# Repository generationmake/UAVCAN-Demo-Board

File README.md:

# UAVCAN-Demo-Board
Board for Arduino Nano 33 IoT and with MCP2515 to demonstrate the functions of UAVCAN

## PCB

### Top

### Bottom

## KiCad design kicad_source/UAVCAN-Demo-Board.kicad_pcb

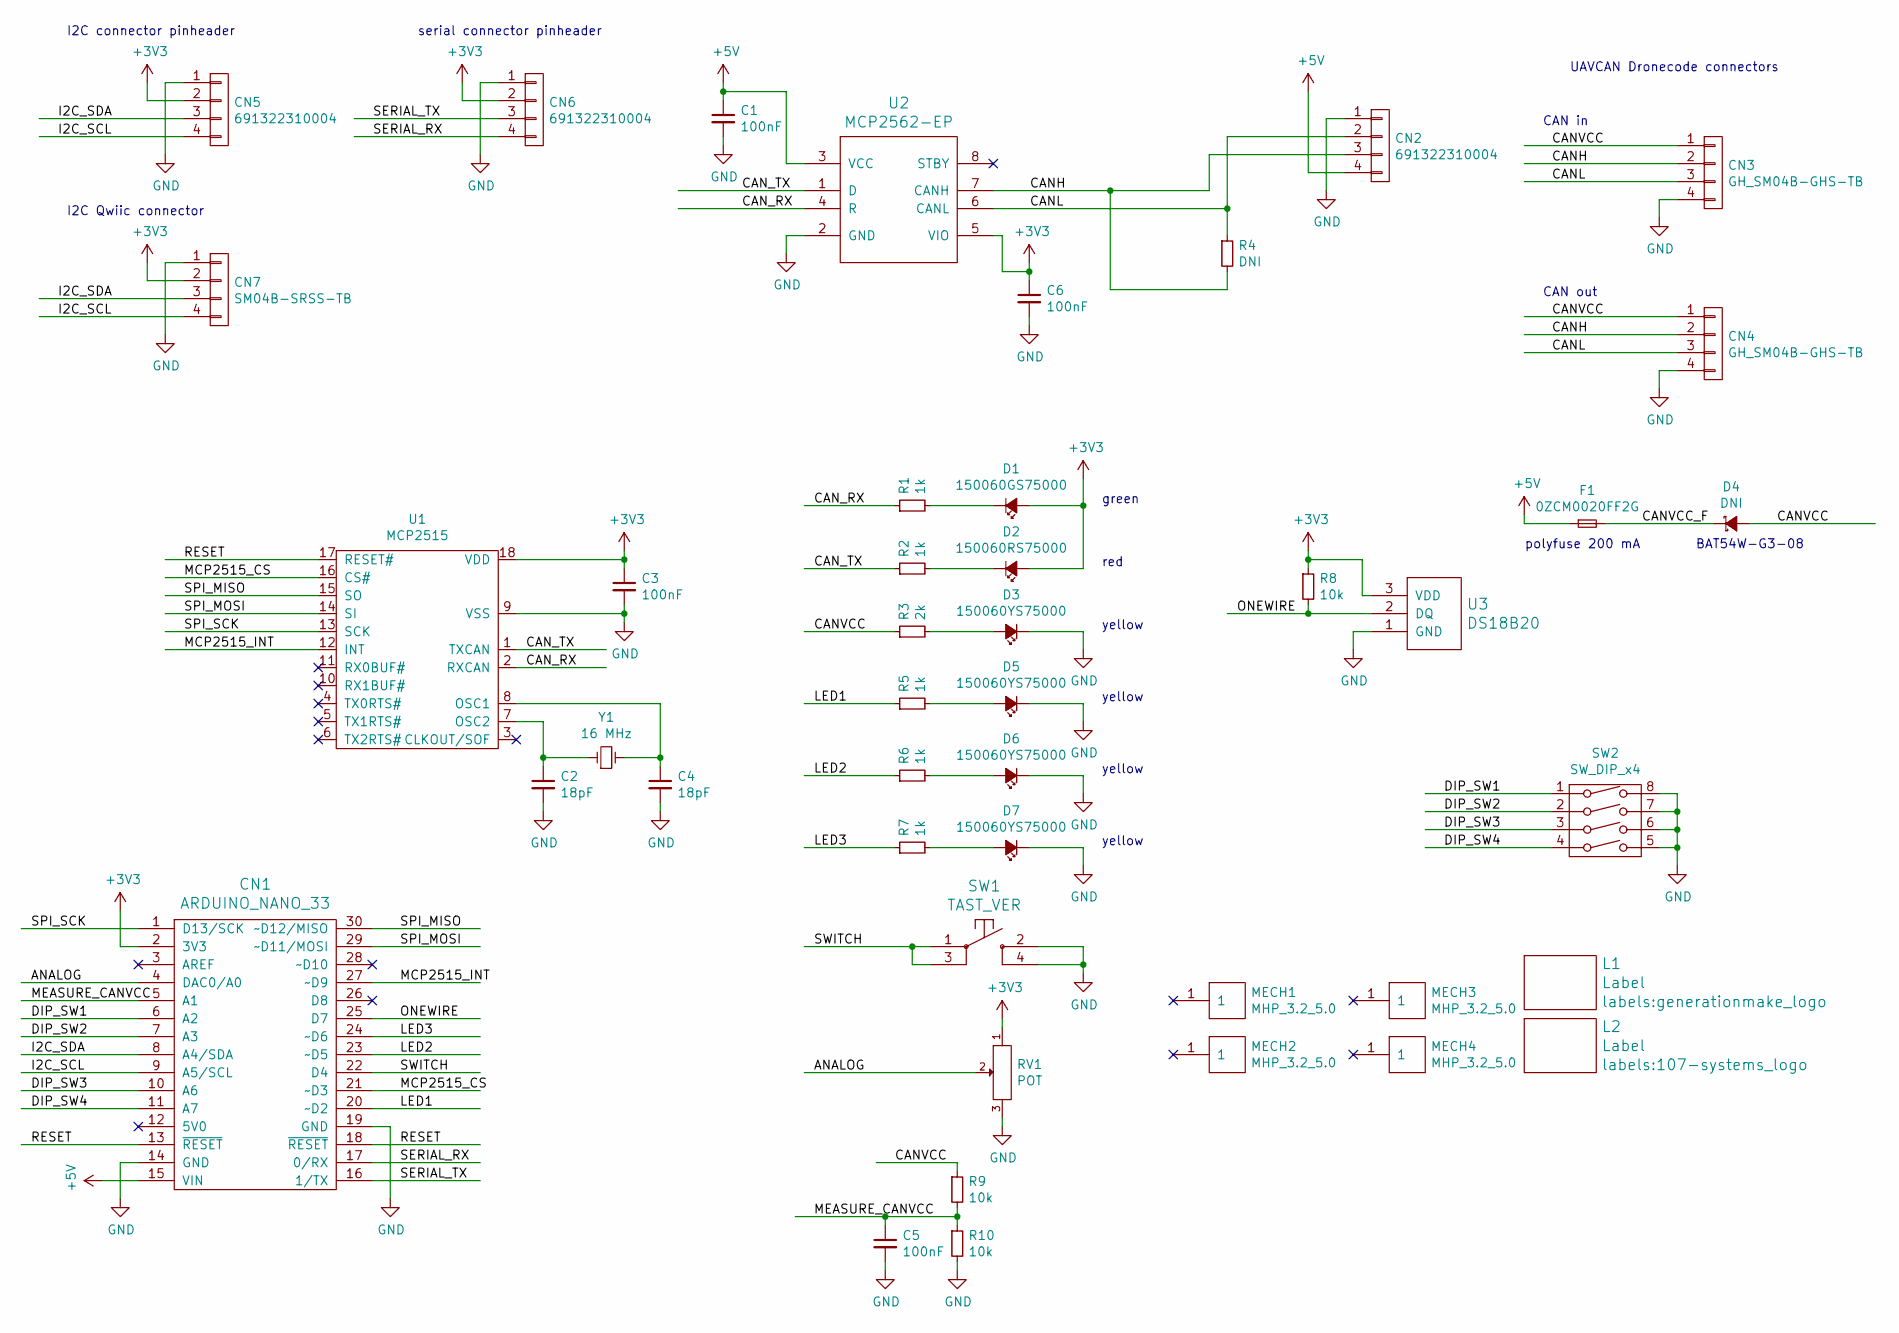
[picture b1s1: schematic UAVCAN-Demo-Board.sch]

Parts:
C1, C3, C5, C6: 100nF; C_Disc_D3.8mm_W2.6mm_P2.50mm
C2, C4: 18pF; C_Disc_D3.8mm_W2.6mm_P2.50mm
CN1: ARDUINO_NANO_33
CN2: 691322310004; WR-TBL_691322310004
CN3, CN4: GH_SM04B-GHS-TB; JST_GH_SM04B-GHS-TB_1x04-1MP_P1.25mm_Horizontal
CN5, CN6: 691322310004; Pin_Header_Straight_1x04
CN7: SM04B-SRSS-TB; JST_SH_SM04B-SRSS-TB_1x04-1MP_P1.00mm_Horizontal
D1: 150060GS75000; LED-5MM
D2: 150060RS75000; LED-5MM
D3, D5, D6, D7: 150060YS75000; LED-5MM
D4: DNI; D_DO-41_SOD81_P7.62mm_Horizontal
F1: 0ZCM0020FF2G; R_Axial_DIN0207_L6.3mm_D2.5mm_P5.08mm_Vertical
L1: Label; generationmake_logo
L2: Label; 107-systems_logo
MECH1, MECH2, MECH3, MECH4: MHP_3.2_5.0
R1, R2, R5, R6, R7: 1k; R_Axial_DIN0207_L6.3mm_D2.5mm_P7.62mm_Horizontal
R3: 2k; R_Axial_DIN0207_L6.3mm_D2.5mm_P7.62mm_Horizontal
R4: DNI; R_Axial_DIN0207_L6.3mm_D2.5mm_P7.62mm_Horizontal
R8, R9, R10: 10k; R_Axial_DIN0207_L6.3mm_D2.5mm_P7.62mm_Horizontal
RV1: POT; Potentiometer_Piher_PT-10-V10_Vertical
SW1: TAST_VER; PCB_PUSH
SW2: SW_DIP_x4; dip_4-300
U1: MCP2515; DIP-18_W7.62mm
U2: MCP2562-EP; DIP-8_W7.62mm
U3: DS18B20; TO-92
Y1: 16 MHz; Crystal_HC49-U_Vertical

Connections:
+3V3: C3.1, C6.1, CN1.2 (3V3), CN5.2, CN6.2, CN7.2, D1.2 (A), D2.2 (A), R8.1, RV1.1, U1.18 (VDD), U2.5 (VIO), U3.3 (VDD)
+5V: C1.1, CN1.15 (VIN), CN2.4, F1.1, U2.3 (VCC)
/ANALOG: CN1.4 (DAC0/A0), RV1.2
/CANH: CN2.3, CN3.2, CN4.2, R4.2, U2.7 (CANH)
/CANL: CN2.2, CN3.3, CN4.3, R4.1, U2.6 (CANL)
/CANVCC: CN3.1, CN4.1, D4.2 (A), R3.1, R9.1
/CANVCC_F: D4.1 (K), F1.2
/CAN_RX: R1.1, U1.2 (RXCAN), U2.4 (R)
/CAN_TX: R2.1, U1.1 (TXCAN), U2.1 (D)
/DIP_SW1: CN1.6 (A2), SW2.1
/DIP_SW2: CN1.7 (A3), SW2.2
/DIP_SW3: CN1.10 (A6), SW2.3
/DIP_SW4: CN1.11 (A7), SW2.4
/I2C_SCL: CN1.9 (A5/SCL), CN5.4, CN7.4
/I2C_SDA: CN1.8 (A4/SDA), CN5.3, CN7.3
/LED1: CN1.20 (~~D2), R5.1
/LED2: CN1.23 (~~D5), R6.1
/LED3: CN1.24 (~~D6), R7.1
/MCP2515_CS: CN1.21 (~~D3), U1.16 (CS#)
/MCP2515_INT: CN1.27 (~~D9), U1.12 (INT)
/MEASURE_CANVCC: C5.1, CN1.5 (A1), R9.2, R10.1
/ONEWIRE: CN1.25 (D7), R8.2, U3.2 (DQ)
/RESET: CN1.13 (~RESET), CN1.18 (~RESET), U1.17 (RESET#)
/SERIAL_RX: CN1.17 (0/RX), CN6.4
/SERIAL_TX: CN1.16 (1/TX), CN6.3
/SPI_MISO: CN1.30 (~~D12/MISO), U1.15 (SO)
/SPI_MOSI: CN1.29 (~~D11/MOSI), U1.14 (SI)
/SPI_SCK: CN1.1 (D13/SCK), U1.13 (SCK)
/SWITCH: CN1.22 (D4), SW1.1, SW1.3
GND: C1.2, C2.2, C3.2, C4.2, C5.2, C6.2, CN1.14 (GND), CN1.19 (GND), CN2.1, CN3.4, CN4.4, CN5.1, CN6.1, CN7.1, D3.1 (K), D5.1 (K), D6.1 (K), D7.1 (K), R10.2, RV1.3, SW1.2, SW1.4, SW2.5, SW2.6, SW2.7, SW2.8, U1.9 (VSS), U2.2 (GND), U3.1 (GND)
unnamed: C2.1, U1.7 (OSC2), Y1.1
unnamed: C4.1, U1.8 (OSC1), Y1.2
unnamed: D1.1 (K), R1.2
unnamed: D2.1 (K), R2.2
unnamed: D3.2 (A), R3.2
unnamed: D5.2 (A), R5.2
unnamed: D6.2 (A), R6.2
unnamed: D7.2 (A), R7.2

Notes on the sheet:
CAN in
UAVCAN Dronecode connectors
CAN out
polyfuse 200 mA
green
red
yellow
BAT54W-G3-08
I2C connector pinheader
I2C Qwiic connector
serial connector pinheader

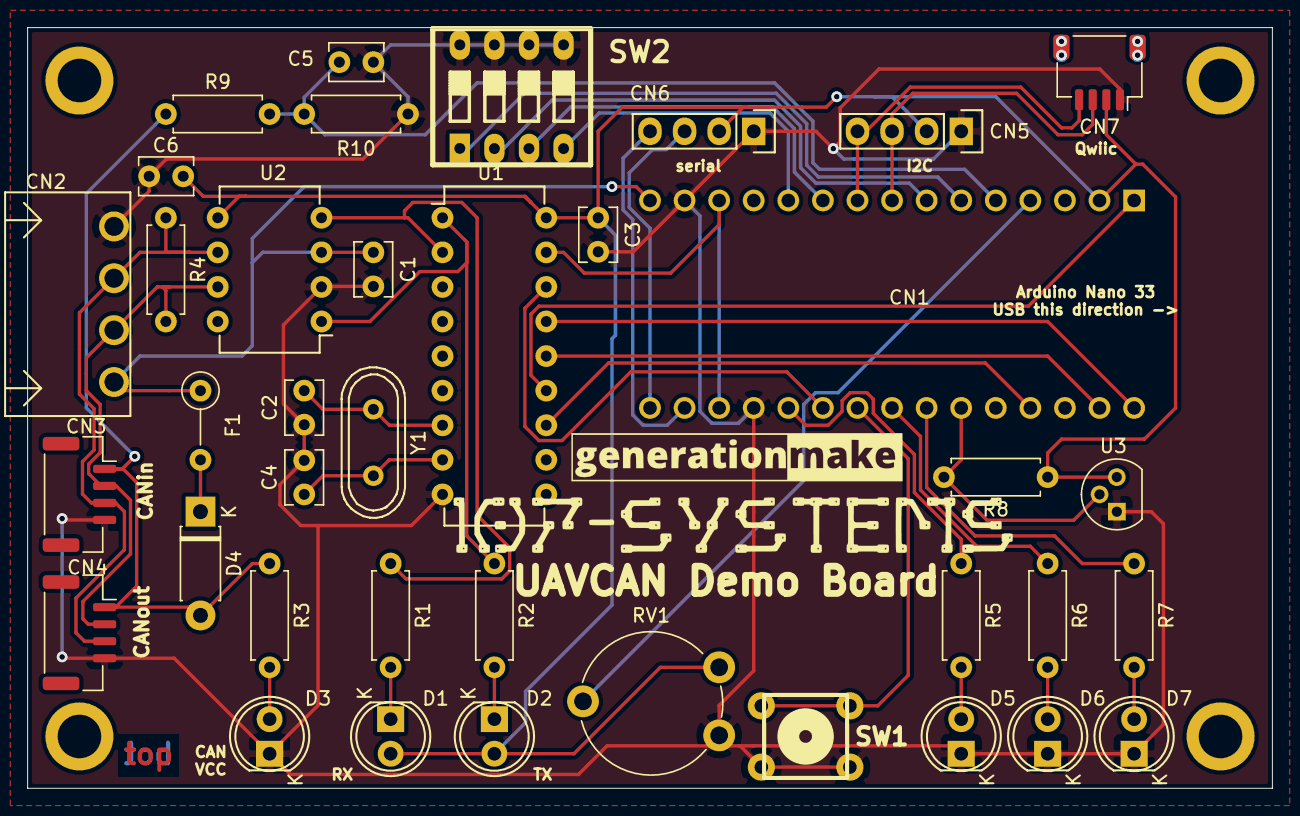
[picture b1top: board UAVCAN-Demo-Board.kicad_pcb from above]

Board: 2 copper layers, 91.4 x 55.9 mm, 44 parts (0 on the bottom side), 38 nets.

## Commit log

2021-03-05 added kicad project
2021-03-05 added schematic pdf
2021-03-05 started layout, added THT parts
2021-03-05 switched to THT parts
2021-03-06 changed DS18B20 to TO-92, cleaned up layout, added labels
2021-03-06 updated pdf schematic and added images
2021-03-06 renamed image files
2021-04-01 updated schematic and layout, added dip switch for configuration, added measurement for CANVCC
2021-04-01 updated schematic pdf and images
2021-04-17 switched CAN transceiver to MCP2562 because of DIP package
2021-04-17 added Qwiic connector
